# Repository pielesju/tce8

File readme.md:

# C74 - Trivial Computation Engine (8bit Computer)

The C74 is a concept for a really simple real 8 bit computer. Real 8 bits because
both busses (data and address) are 8 bit.
I had the idea for this project while developing an emulator for this imaginary machine.

## Project Roadmap

- Creating the logic
- Building and testing the components (memory, alu, etc.) in Hardware one by one
- Building the whole system

_Another sideproject could be developing an Assembler and maybe a programming language_

## OP Codes

```
00000000 NOP
00000001 HLT
00000010 STD
00000011 LDD
00000100 STX
00000101 LDX
00000110 STY
00000111 LDY
00001000 LDA
00001001 ADD
00001010 SUB
00001011 AND
00001100 OR
00001101 XOR
00001110 NOT
00001111 JMP
00010000 IN
00010001 OUT
```

## Microinstructions

```
00000 HALT

PROGRAM COUNTER INSTRUCTIONS
00001 PC_EN
00010 PC_COUNT
00011 PC_JUMP

ALU INSTRUCTIONS
00100 ALU_EN
00101 ALU_CTRL0
00110 ALU_CTRL1
00111 ALU_CTRL2

MEMORY INSTRUCTIONS
01000 MEM_WRITE
01001 MEM_READ

REGISTER INSTRUCTIONS
01010 X_WRITE
01011 X_READ
01100 Y_WRITE
01101 Y_READ
01110 A_WRITE
01111 A_READ
10000 I_WRITE
10001 I_READ
10010 DATA_WRITE
10011 DATA_READ
10100 ADDR_WRITE
10101 ADDR_READ
10110 IN_WRITE
10111 IN_READ
11000 OUT_WRITE
11001 OUT_READ

CU INSTRUCTIONS
11010 STEP_RESET
```

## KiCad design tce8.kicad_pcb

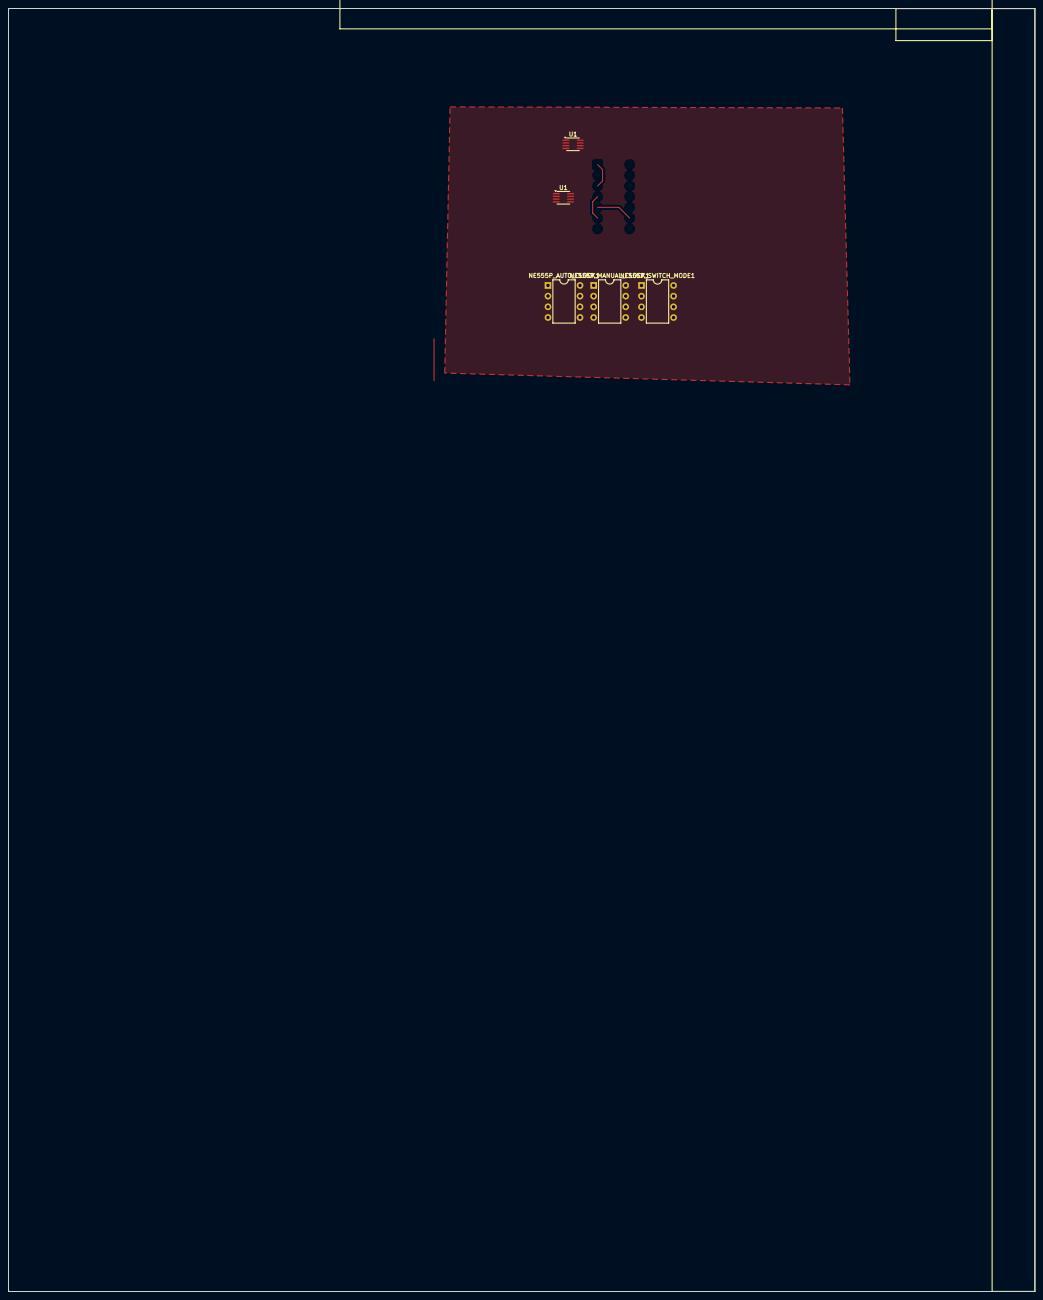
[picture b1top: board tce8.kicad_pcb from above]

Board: 4 copper layers, 243.8 x 304.8 mm, 5 parts (0 on the bottom side), 7 nets.

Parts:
NE555P_AUTO_CLOCK1, NE555P_MANUAL_CLOCK1, NE555P_SWITCH_MODE1: NE555P; DIP-8_W7.62mm
U1, U1#2: 74LS32; SSOP-8_2.95x2.8mm_P0.65mm

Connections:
B: U1.1, U1#2.1
Cin: U1.4, U1#2.4
unnamed: NE555P_MANUAL_CLOCK1.6 (THR), NE555P_MANUAL_CLOCK1.7 (DIS)
unnamed: NE555P_MANUAL_CLOCK1.4 (R), NE555P_MANUAL_CLOCK1.8 (VCC)
unnamed: U1.3, U1#2.3
unnamed: U1.6, U1#2.6
SUB: U1.2, U1.5, U1#2.2, U1#2.5

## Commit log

2024-07-16 deleted empty file
2024-07-16 deleted unneeded files
2024-07-16 added readme file
2024-07-16 KiCAD Design files
2024-10-01 one bit alu
2024-10-02 1 bit alu
2025-05-16 helper programs
